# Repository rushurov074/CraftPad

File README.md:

# CraftPad

This is my submission for the Hack Club Hackpad event! The CraftPad is a custom designed 9-key macropad built using a Seeed XIAO RP2040 and QMK firmware, specifically programmed to launch applications like Discord and Minecraft.

## Screenshots

### Overall Hackpad

### Schematic

### PCB

## Bill of Materials (BOM)
* 1x Seeed Studio XIAO RP2040
* 9x MX-style Mechanical Switches
* 9x White Blank DSA Keycaps
* 20x Through-hole 1N4148 Diodes
* 20x SK6812 MINI-E LEDs
* 6x M3x16mm Screws
* 6x M3x5mmx4mm Heat-set Inserts

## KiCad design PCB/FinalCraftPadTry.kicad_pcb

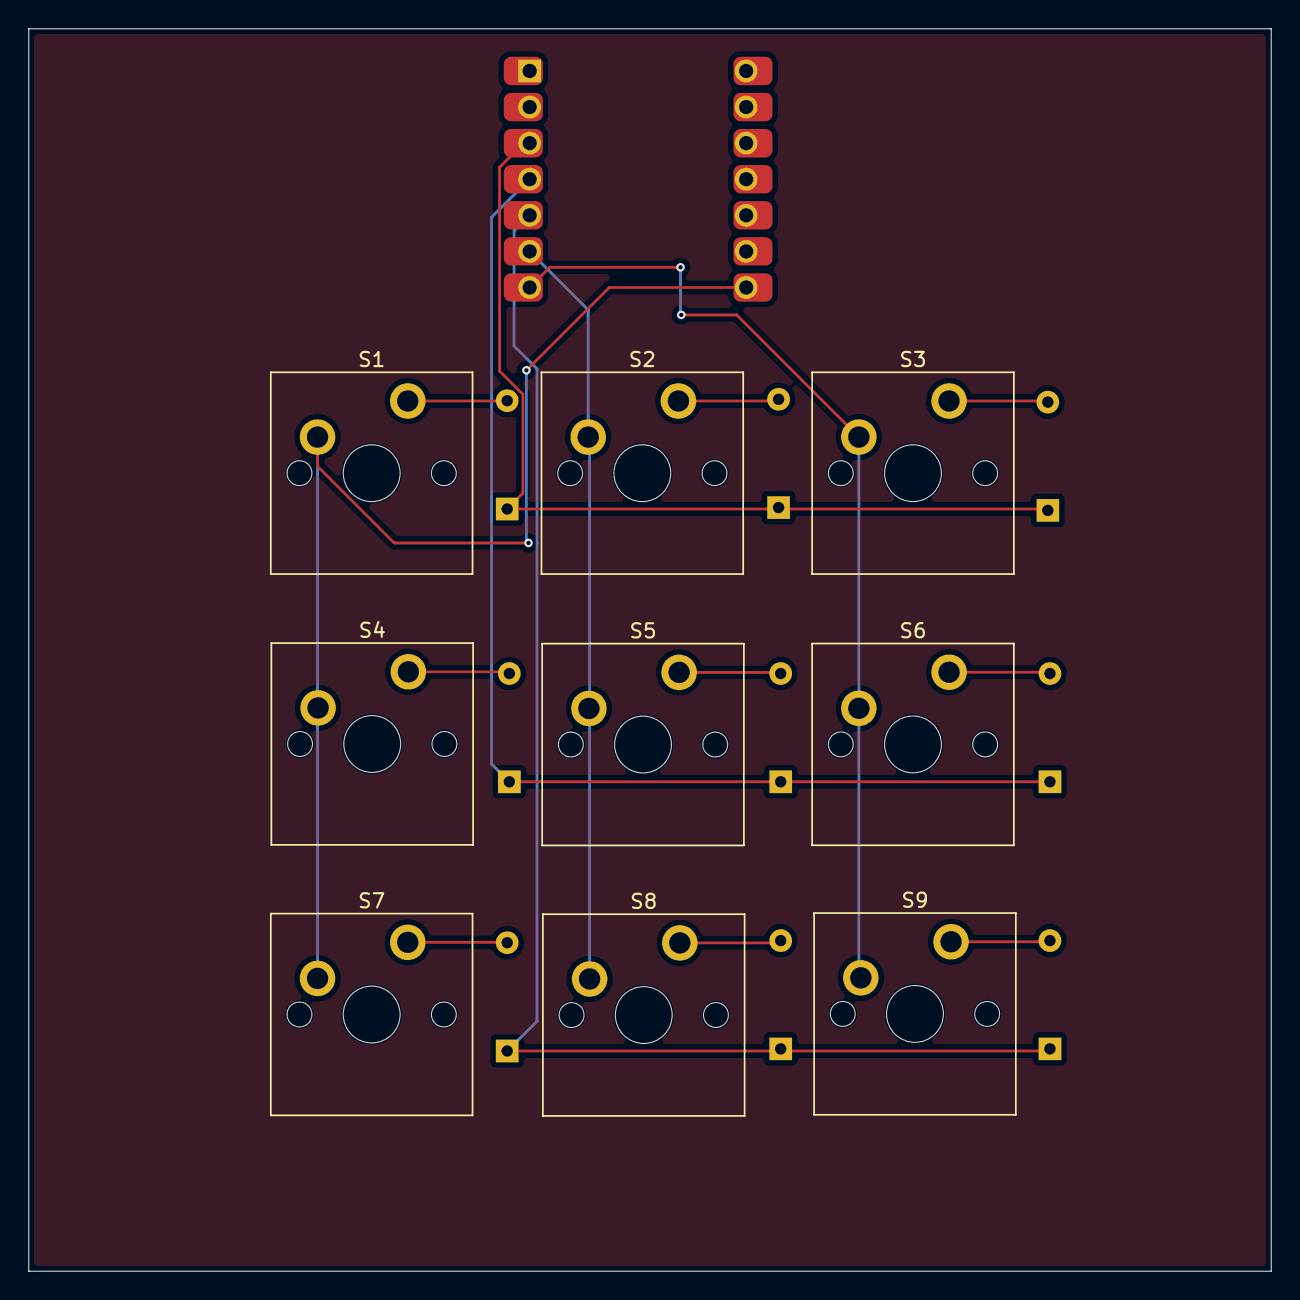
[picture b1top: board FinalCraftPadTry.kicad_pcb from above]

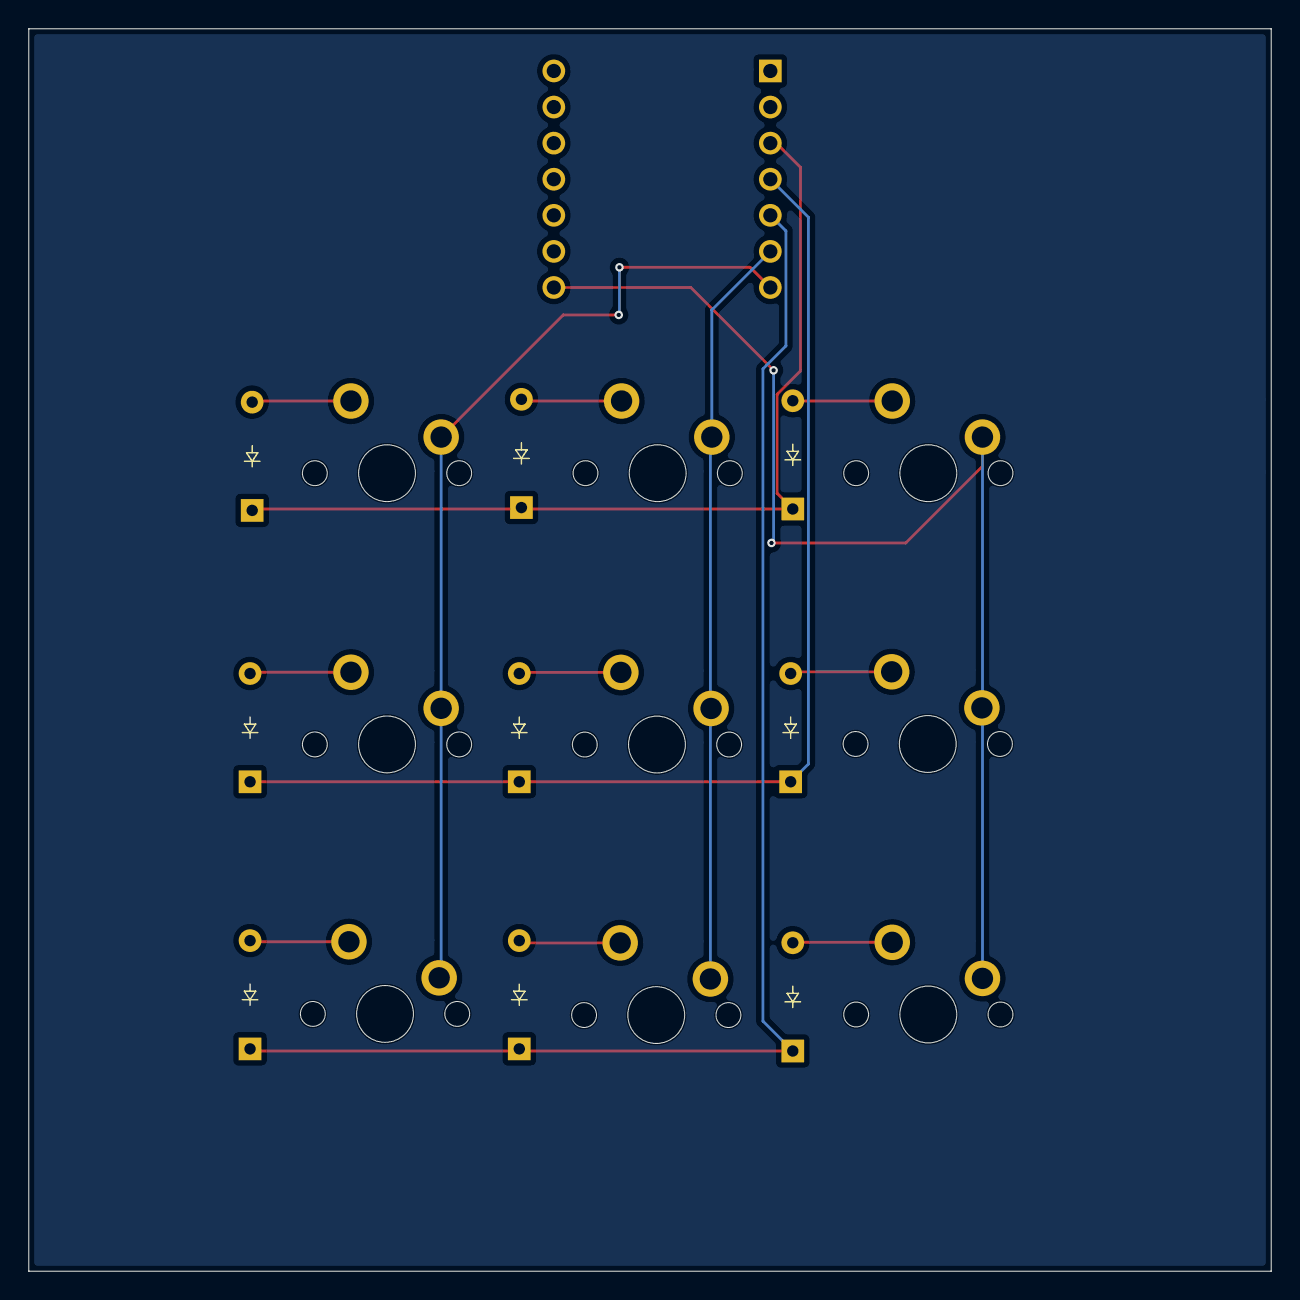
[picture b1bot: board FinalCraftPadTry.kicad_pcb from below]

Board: 2 copper layers, 87.5 x 87.5 mm, 19 parts (9 on the bottom side), 15 nets.

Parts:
D1, D2, D3, D4, D5, D6, D7, D8, D9: Diode_DO-35
S1, S2, S3, S4, S5, S6, S7, S8, S9: MX_PCB_1.00u
U1: MCU_Seeed_XIAO_RP2040; Seeed_XIAO_RP2040

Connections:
Column 0: S1.1, S4.1, S7.1, U1.8 (PB09_A7_D7_RX)
Column 1: S2.1, S5.1, S8.1, U1.6 (PA9_A5_D5_SCL)
Column 2: S3.1, S6.1, S9.1, U1.7 (PB08_A6_D6_TX)
unnamed: D1.2 (A), S1.2
unnamed: D2.2 (A), S2.2
unnamed: D3.2 (A), S3.2
unnamed: D4.2 (A), S4.2
unnamed: D5.2 (A), S5.2
unnamed: D6.2 (A), S6.2
unnamed: D7.2 (A), S7.2
unnamed: D8.2 (A), S8.2
unnamed: D9.2 (A), S9.2
Row 0: D1.1 (K), D2.1 (K), D3.1 (K), U1.3 (PA10_A2_D2)
Row 1: D4.1 (K), D5.1 (K), D6.1 (K), U1.4 (PA11_A3_D3)
Row 2: D7.1 (K), D8.1 (K), D9.1 (K), U1.5 (PA8_A4_D4_SDA)

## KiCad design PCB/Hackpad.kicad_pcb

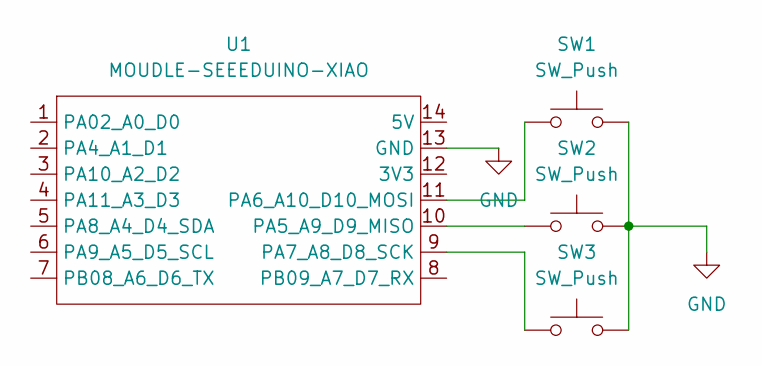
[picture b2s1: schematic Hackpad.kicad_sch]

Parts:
SW1, SW2, SW3: SW_Push; SW_Cherry_MX_1.00u_PCB
U1: MOUDLE-SEEEDUINO-XIAO; XIAO-Generic-Hybrid-14P-2.54-21X17.8MM

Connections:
GND: SW1.2, SW2.2, SW3.2, U1.13 (GND)
unnamed: SW2.1, U1.10 (PA5_A9_D9_MISO)
unnamed: SW1.1, U1.11 (PA6_A10_D10_MOSI)
unnamed: SW3.1, U1.9 (PA7_A8_D8_SCK)

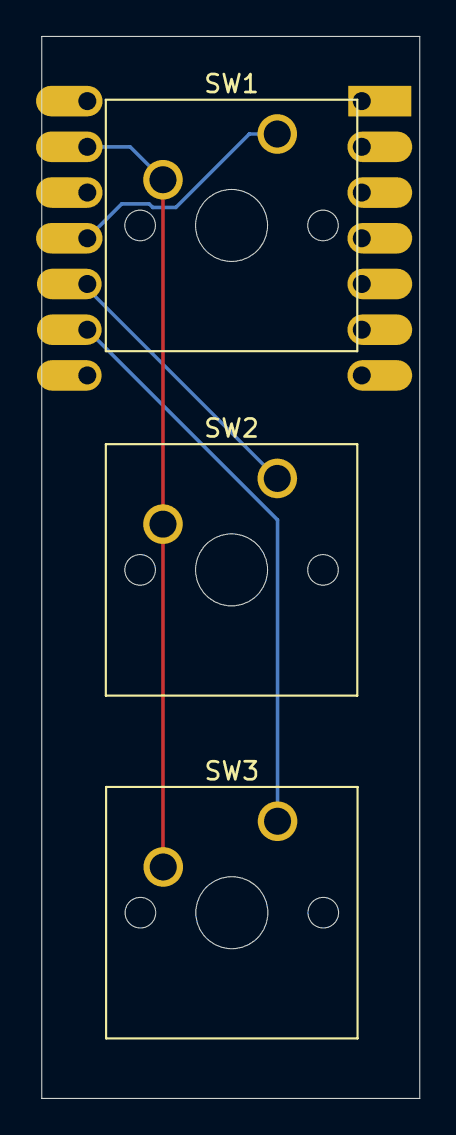
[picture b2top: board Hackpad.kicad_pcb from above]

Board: 2 copper layers, 21.0 x 59.0 mm, 4 parts (1 on the bottom side), 4 nets.
